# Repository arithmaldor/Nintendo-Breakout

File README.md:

# Copyright and Disclaimer
Copyright: Jacob Proctor

This documentation describes Open Hardware and is licensed under the
CERN OHL v. 1.2.

You may redistribute and modify this documentation under the terms of the
CERN OHL v.1.2. (http://ohwr.org/cernohl). This documentation is distributed
WITHOUT ANY EXPRESS OR IMPLIED WARRANTY, INCLUDING OF
MERCHANTABILITY, SATISFACTORY QUALITY AND FITNESS FOR A
PARTICULAR PURPOSE. Please see the CERN OHL v.1.2 for applicable
conditions

# Nintendo Multi-out Breakout
Breaks out all of the signals from the Nintendo Muliout so you can easily access them. 

# Operation
Plug in and go. There is a solder jumper to set the csync coming from the HD-15 port as TTL or 75ohm. Closed is TTL, open is 75 ohm. If you only plan to use this in TTL mode the resistor is not required.
This adapter can only break out signals that are already present. Unmodded SNES Jr. will only output composite, unmodded N64's will only ouput CVBS and S-video, same for Gamecube.
A cool extra feature is that this breakout lets you easily output component YPbPr from the GCDual and N64Advanced mods.

# PAL Systems
This was designed with NTSC systems in mind and is not compatible with PAL systems.

# Parts
Refer to BOM.csv for all components. For the support leg, use any appropriately long brass/metal m3 standoff/pillar and screw a rubber foot to the bottom. Solder a 5mm spring clamp to the bottom of the board to adjust the height.
For a Gamecube with Gameboy Player, standoffs may need to be screwed into each other (stacked) to reach the needed height.

# Case
The incredible [Magic Trashman](https://twitter.com/MagicTrashman) was kind enough to design 3D printable cases for both my Nintendo and PSX breakouts. They are under the same license as the PCB and are free to use, but if you order through thingiverse you can leave him a nice tip. Current designs fit the height of the original PS1 and the original SNES, but can be easily adjusted for height if you have some basic 3D design skills. They are held together with 2x 14mm M3 machine screws.
Pictures: https://t.co/ojJ8epfZXH?amp=1
Thingiverse: https://t.co/7dF171BqaF?amp=1
Bonus: If you plug the Nintendo/Sony connector into the console and screw the PCB into the bottom of the case, it makes it a lot easier to solder the connector to the board as it is held in place.

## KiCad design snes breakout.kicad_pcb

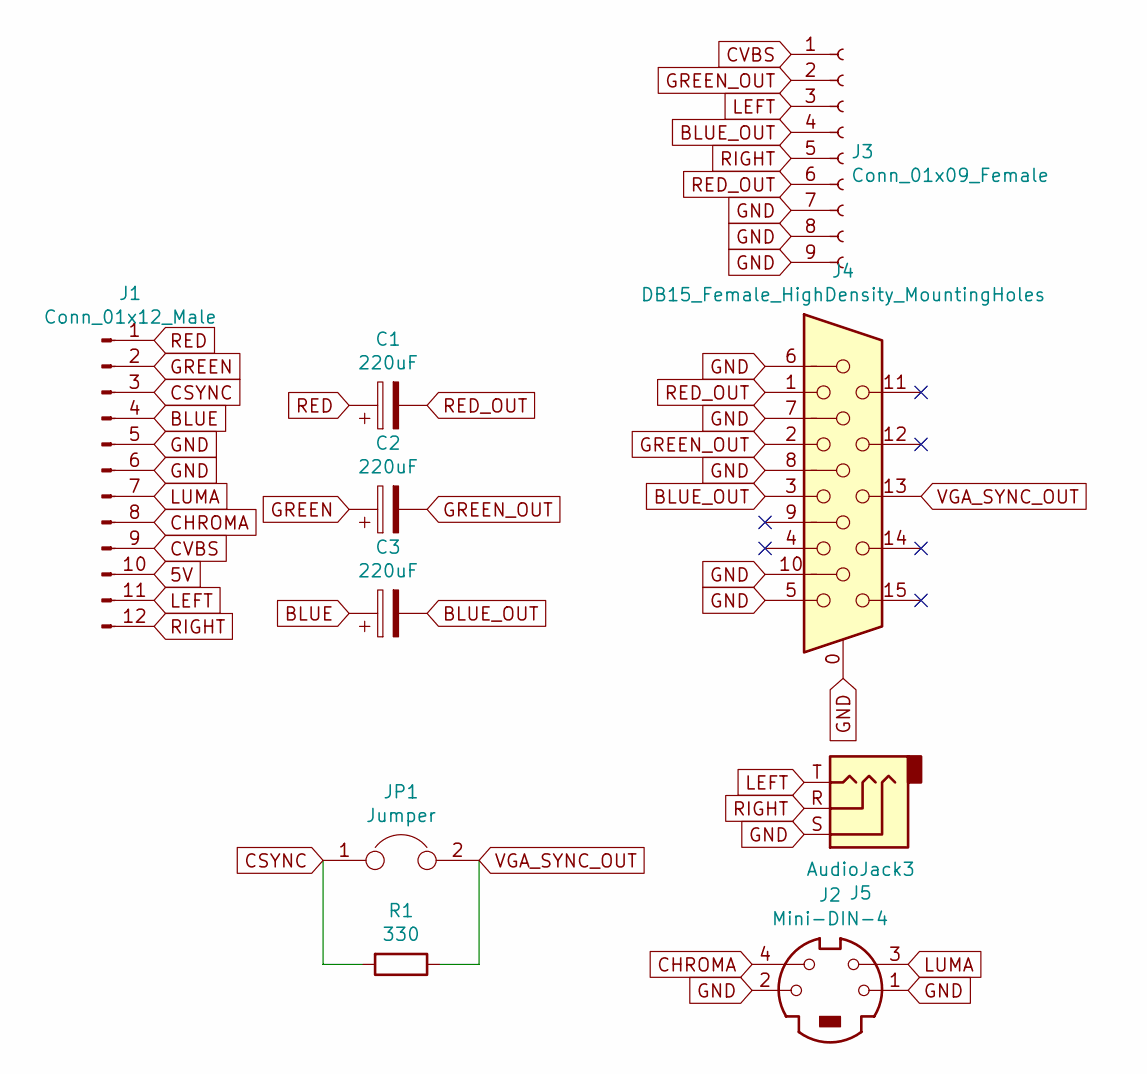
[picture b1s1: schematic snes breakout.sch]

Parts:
C1, C2, C3: 220uF; CP_Elec_6.3x5.4
J1: Conn_01x12_Male; SNES_PLUG
J2: Mini-DIN-4; CUI_MD-40SG
J3: Conn_01x09_Female; 3x2_RCA
J4: DB15_Female_HighDensity_MountingHoles; VGA
J5: AudioJack3; CUI_SJ1-3533NG
JP1: Jumper; SolderJumper-2_P1.3mm_Open_TrianglePad1.0x1.5mm
R1: 330; R_0603_1608Metric_Pad1.05x0.95mm_HandSolder

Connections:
5V: J1.10
BLUE: C3.1, J1.4
BLUE_OUT: C3.2, J3.4, J4.3
CHROMA: J1.8, J2.4
CSYNC: J1.3, JP1.1, R1.2
CVBS: J1.9, J3.1
GND: J1.5, J1.6, J2.1, J2.2, J3.7, J3.8, J3.9, J4.0, J4.5, J4.6, J4.7, J4.8, J4.10, J5.S
GREEN: C2.1, J1.2
GREEN_OUT: C2.2, J3.2, J4.2
LEFT: J1.11, J3.3, J5.T
LUMA: J1.7, J2.3
RED: C1.1, J1.1
RED_OUT: C1.2, J3.6, J4.1
RIGHT: J1.12, J3.5, J5.R
VGA_SYNC_OUT: J4.13, JP1.2, R1.1

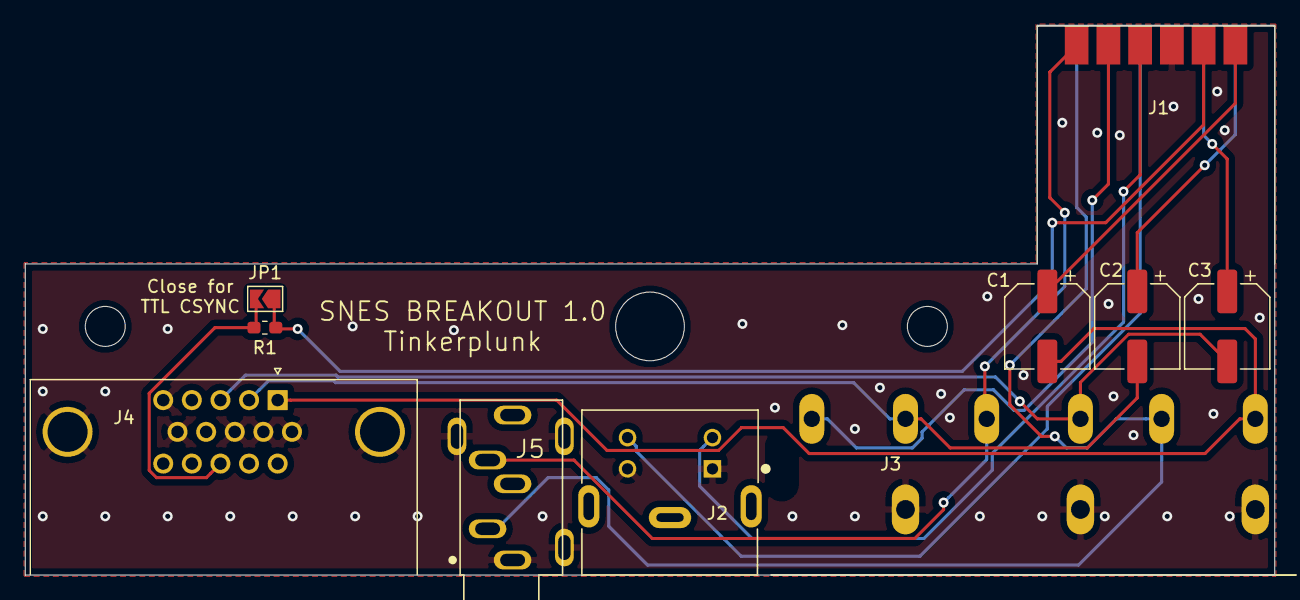
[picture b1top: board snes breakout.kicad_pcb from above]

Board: 2 copper layers, 100.0 x 44.0 mm, 10 parts (0 on the bottom side), 14 nets.

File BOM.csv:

Reference,Value,Footprint,MPN,Datasheet,Link,Alt Link,Alt Link 2,Qty
C1-C3,220uF,6.3x5.4mm,EEE0JA221WP,"https://media.digikey.com/pdf/Data%20Sheets/Panasonic%20Elec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,Type_V_Rev2018.pdf",https://www.digikey.com/product-detail/en/panasonic-electron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,https://lcsc.com/product-detail/Aluminum-Electrolytic-Capaci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,,3
J1,Nintendo Multiout Connector,,,,https://console5.com/store/nintendo-snes-super-famicom-n64-a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, , ,1
J2,S-Video,Mini Din 4,"MD-40
S, SG, SM or SGK",http://service.powerdynamics.com/ec/Catalog17/Section%2011.pdf,https://www.digikey.com/product-detail/en/cui-inc/MD-40SM/CP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,https://www.arrow.com/en/products/md-40sm/cui-inc, ,1
J3,Headphone Jack,3 pin,SJ1-3533NG,https://www.cui.com/product/resource/digikeypdf/sj1-353xng.pdf,https://www.digikey.com/product-detail/en/cui-inc/SJ1-3533NG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,https://www.arrow.com/en/products/sj1-3533ng/cui-inc,https://lcsc.com/product-detail/Audio-Video-Connectors_Boom-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,1
J4,DB15 Female High Density,DB15 HD Female,ICD15S13E6GV00LF,https://www.amphenol-icc.com/media/wysiwyg/files/drawing/c-c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,https://www.digikey.com/product-detail/en/amphenol-icc-fci/I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,https://www.arrow.com/en/products/icd15s13e6gv00lf/amphenol-fci,https://lcsc.com/product-detail/D-Sub-Connectors_VGA-002_C13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,1
J5,3x2_RCA,"Stacked RCA 2 high 3 long. LR,TB: GBRYWR",RCA-628N1-14,,https://ebay.us/PmOF6q, ,,1
R1,330 Ohm,Metric 0603,RC0603FR-07330RL,http://www.yageo.com/documents/recent/PYu-RC_Group_51_RoHS_L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,https://www.digikey.com/product-detail/en/yageo/RC0603FR-073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,https://lcsc.com/product-detail/Chip-Resistor-Surface-Mount_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,,1

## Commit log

2019-07-02 finished schematic, started board layout
2019-07-03 laid outline, placed components
2019-07-03 Laid tracks, generated gerbers
2019-07-08 Generated gerbers
2019-07-31 Fixed footprints
    Need to redo routing
2019-08-02 Fixes
    Fixed routing, removed some mask on the bottom to solder the spring on. Ready for action.
2019-08-02 Finishing touches
    added renders and photos, BOM, license, etc.
2019-09-09 Added case links
